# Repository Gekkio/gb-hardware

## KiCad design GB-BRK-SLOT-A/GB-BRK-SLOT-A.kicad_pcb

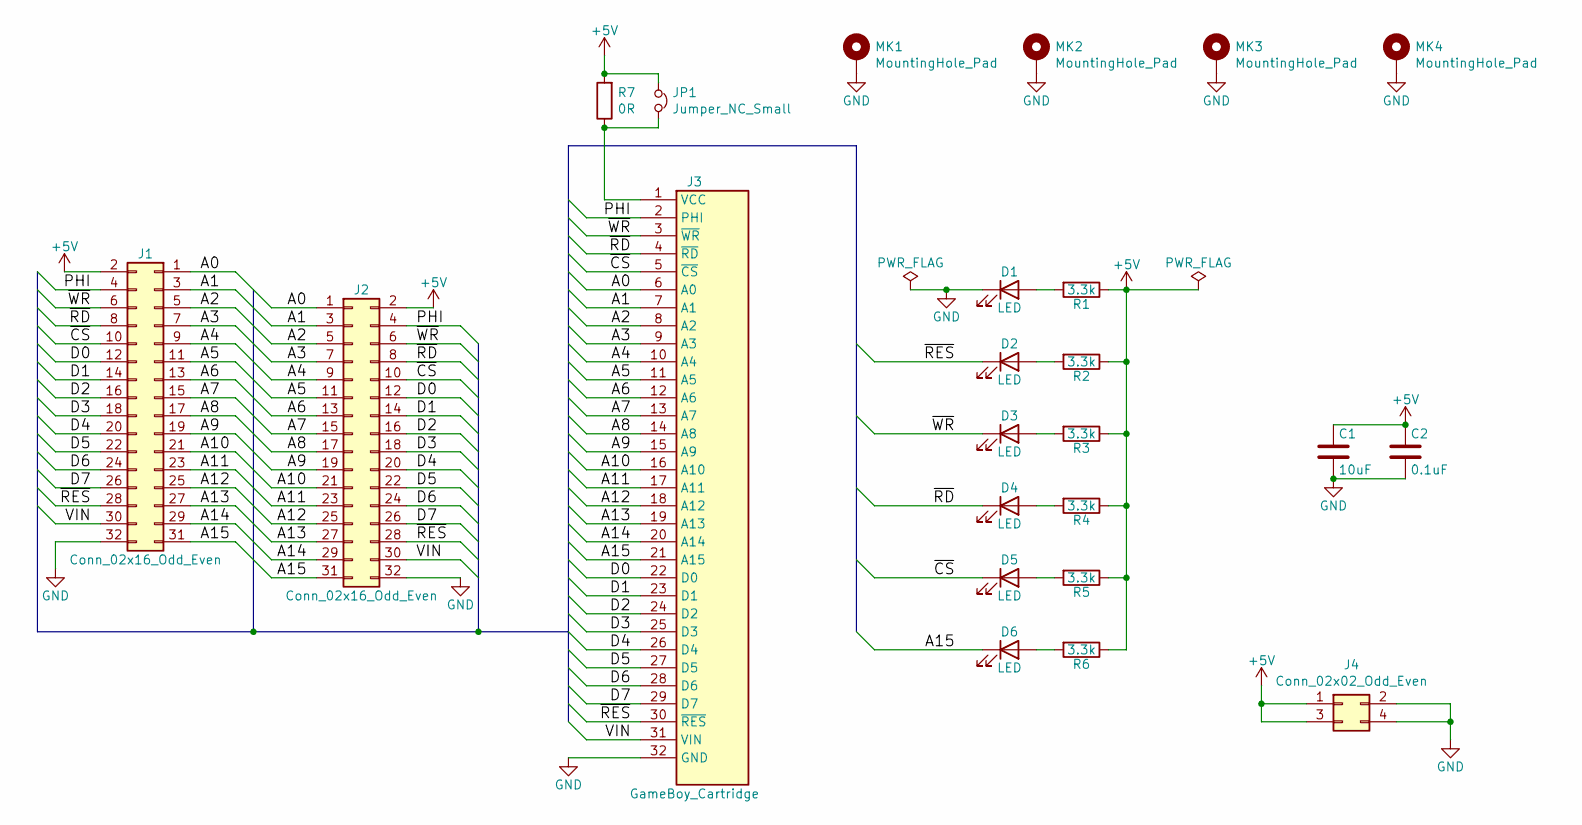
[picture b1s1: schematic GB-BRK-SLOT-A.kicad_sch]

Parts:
C1: 10uF; C_1206_3216Metric
C2: 0.1uF; C_0603_1608Metric
D1, D2, D3, D4, D5, D6: LED; LED_0603_1608Metric
J1: Conn_02x16_Odd_Even; PinSocket_2x16_P2.54mm_Vertical
J2: Conn_02x16_Odd_Even; PinHeader_2x16_P2.54mm_Vertical
J3: GameBoy_Cartridge; GameBoy_Cartridge_DMG_1x32_P1.50mm_Socket_Horizontal
J4: Conn_02x02_Odd_Even; PinHeader_2x02_P2.54mm_Vertical
JP1: Jumper_NC_Small; PinHeader_1x02_P2.54mm_Vertical
MK1, MK2, MK3, MK4: MountingHole_Pad; MountingHole_3.2mm_M3_Pad_Via
R1, R2, R3, R4, R5, R6: 3.3k; R_0603_1608Metric
R7: 0R; R_1206_3216Metric_Pad1.42x1.75mm_HandSolder

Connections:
+5V: C1.1, C2.1, J1.2, J2.2, J4.1, J4.3, JP1.1, R1.1, R2.1, R3.1, R4.1, R5.1, R6.1, R7.2
/A0: J1.1, J2.1, J3.6 (A0)
/A1: J1.3, J2.3, J3.7 (A1)
/A2: J1.5, J2.5, J3.8 (A2)
/A3: J1.7, J2.7, J3.9 (A3)
/A4: J1.9, J2.9, J3.10 (A4)
/A5: J1.11, J2.11, J3.11 (A5)
/A6: J1.13, J2.13, J3.12 (A6)
/A7: J1.15, J2.15, J3.13 (A7)
/A8: J1.17, J2.17, J3.14 (A8)
/A9: J1.19, J2.19, J3.15 (A9)
/A10: J1.21, J2.21, J3.16 (A10)
/A11: J1.23, J2.23, J3.17 (A11)
/A12: J1.25, J2.25, J3.18 (A12)
/A13: J1.27, J2.27, J3.19 (A13)
/A14: J1.29, J2.29, J3.20 (A14)
/A15: D6.1 (K), J1.31, J2.31, J3.21 (A15)
/D0: J1.12, J2.12, J3.22 (D0)
/D1: J1.14, J2.14, J3.23 (D1)
/D2: J1.16, J2.16, J3.24 (D2)
/D3: J1.18, J2.18, J3.25 (D3)
/D4: J1.20, J2.20, J3.26 (D4)
/D5: J1.22, J2.22, J3.27 (D5)
/D6: J1.24, J2.24, J3.28 (D6)
/D7: J1.26, J2.26, J3.29 (D7)
/PHI: J1.4, J2.4, J3.2 (PHI)
/VIN: J1.30, J2.30, J3.31 (VIN)
/~CS: D5.1 (K), J1.10, J2.10, J3.5 (~CS)
/~RD: D4.1 (K), J1.8, J2.8, J3.4 (~RD)
/~RES: D2.1 (K), J1.28, J2.28, J3.30 (~RES)
/~WR: D3.1 (K), J1.6, J2.6, J3.3 (~WR)
GND: C1.2, C2.2, D1.1 (K), J1.32, J2.32, J3.32 (GND), J4.2, J4.4, MK1.1, MK2.1, MK3.1, MK4.1
unnamed: D1.2 (A), R1.2
unnamed: D2.2 (A), R2.2
unnamed: D3.2 (A), R3.2
unnamed: D4.2 (A), R4.2
unnamed: D5.2 (A), R5.2
unnamed: D6.2 (A), R6.2
unnamed: J3.1 (VCC), JP1.2, R7.1

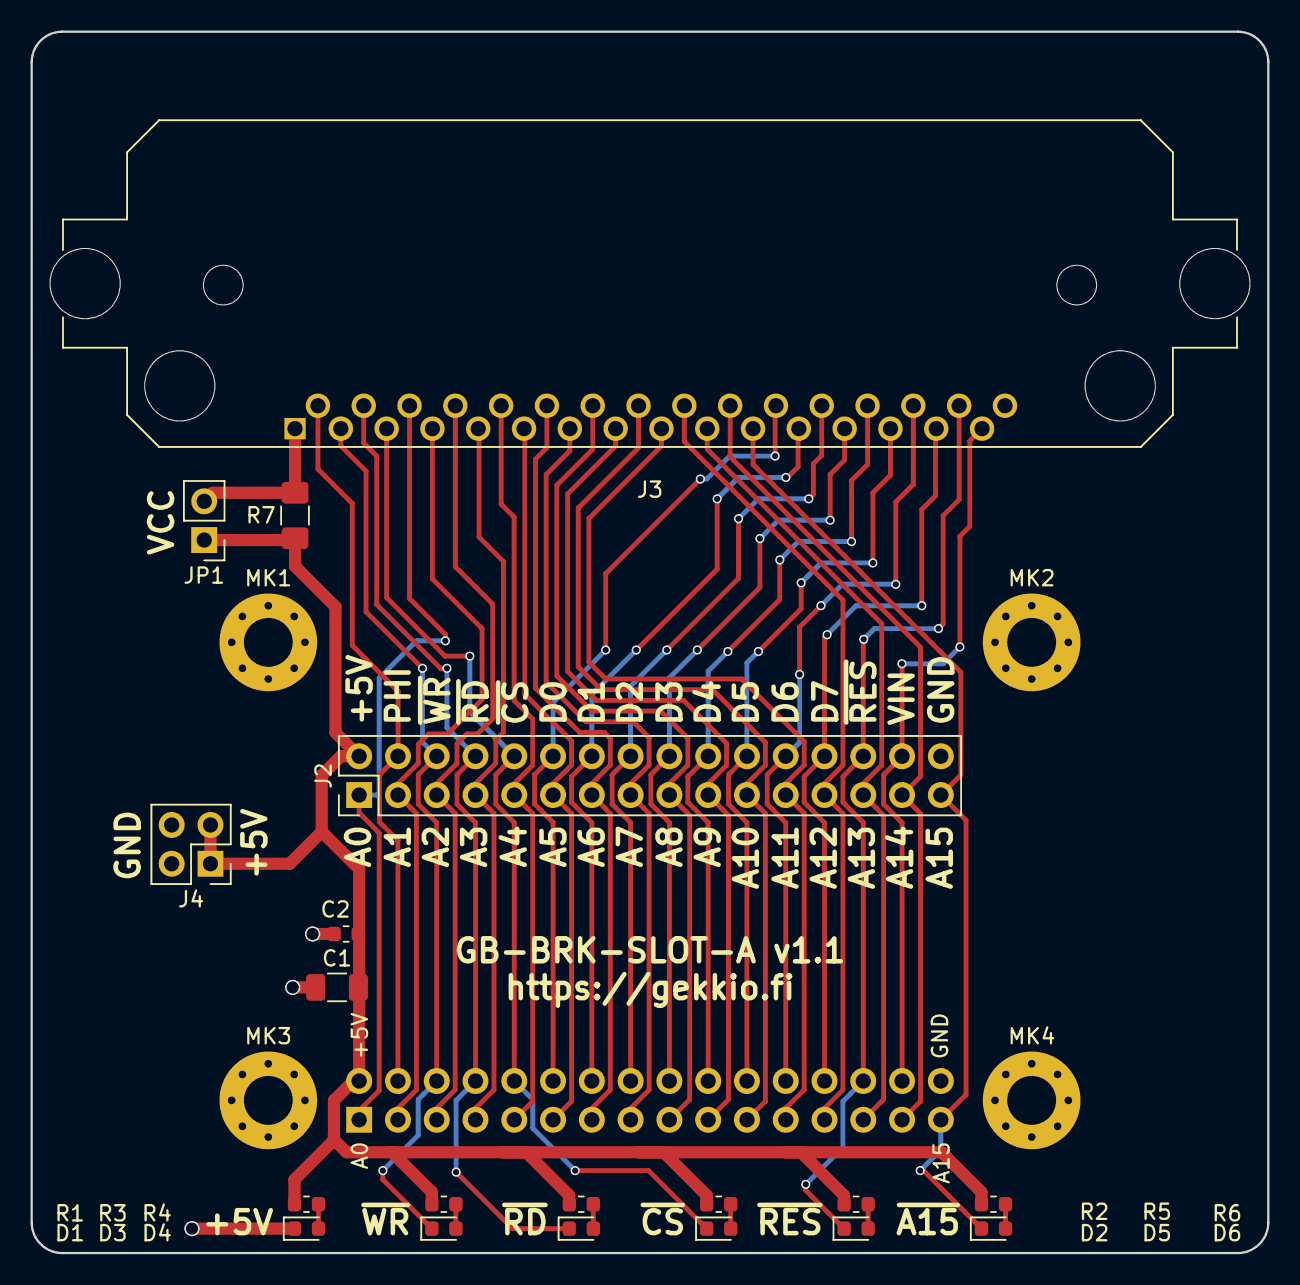
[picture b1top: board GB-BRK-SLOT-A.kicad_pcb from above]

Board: 2 copper layers, 81.0 x 80.0 mm, 24 parts (1 on the bottom side), 39 nets.

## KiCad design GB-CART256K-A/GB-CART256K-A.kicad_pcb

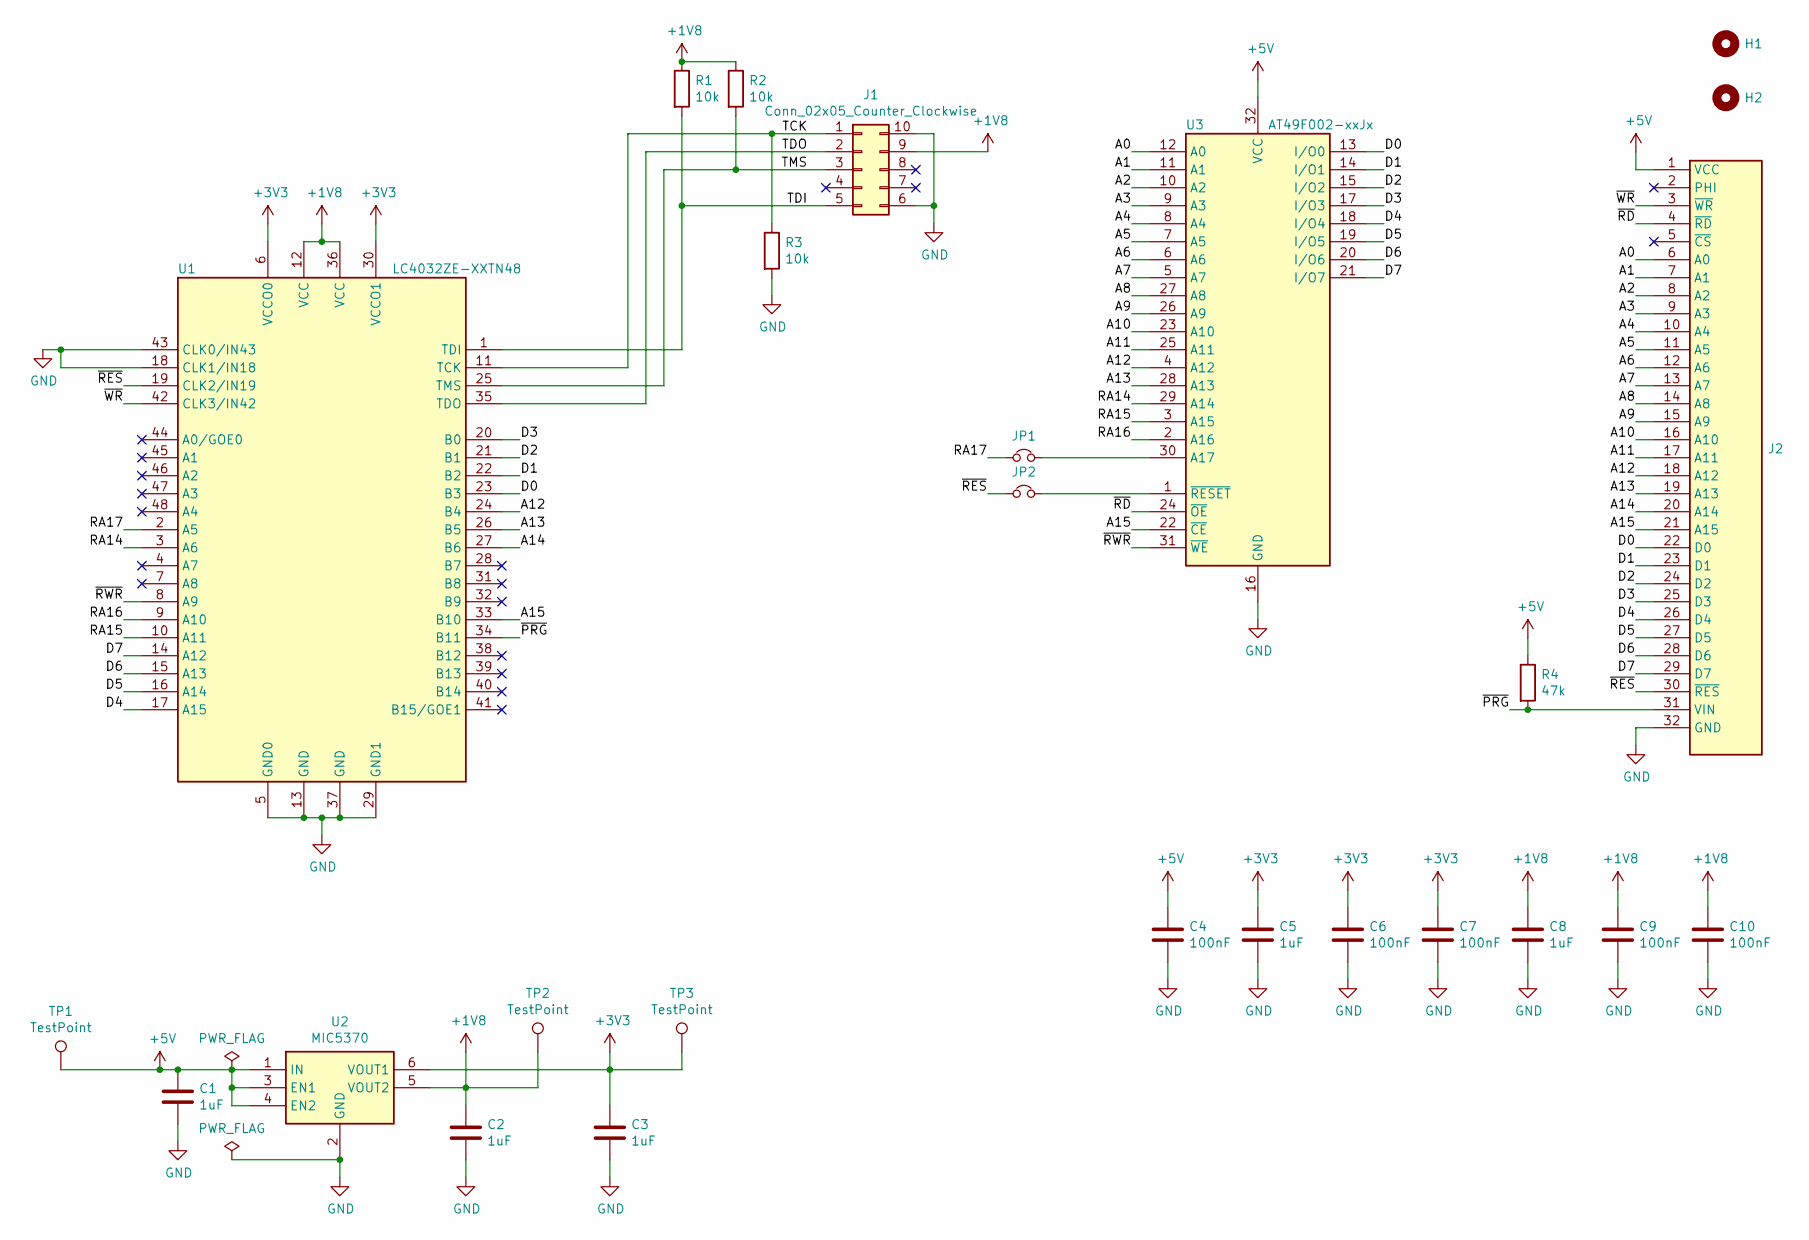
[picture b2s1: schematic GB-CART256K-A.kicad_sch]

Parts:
C1, C2, C3, C5, C8: 1uF; C_0805_2012Metric
C4, C6, C7, C9, C10: 100nF; C_0603_1608Metric
H1: DNF; MountingHole_7.2mm
H2: DNF; MountingHole_2.3mm
J1: Conn_02x05_Counter_Clockwise; Tag-Connect_TC2050-IDC-NL_2x05_P1.27mm_Vertical
J2: DNF; GameBoy_Cartridge_1x32_P1.50mm_Edge
JP1, JP2: DNF; SolderJumper-2_P1.3mm_Open_RoundedPad1.0x1.5mm
R1, R2, R3: 10k; R_0603_1608Metric
R4: 47k; R_0603_1608Metric
TP1, TP2, TP3: TestPoint; TestPoint_THTPad_D2.0mm_Drill1.0mm
U1: LC4032ZE-XXTN48; TQFP-48_7x7mm_P0.5mm
U2: MIC5370; MLF-6-1EP_1.6x1.6mm_P0.5mm_EP0.5x1.26mm
U3: AT49F002-xxJx; PLCC-32_11.4x14.0mm_P1.27mm

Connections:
+1V8: C2.1, C8.1, C9.1, C10.1, J1.9, R1.1, R2.1, TP2.1, U1.12 (VCC), U1.36 (VCC), U2.5 (VOUT2)
+3V3: C3.1, C5.1, C6.1, C7.1, TP3.1, U1.6 (VCCO0), U1.30 (VCCO1), U2.6 (VOUT1)
+5V: C1.1, C4.1, J2.1 (VCC), R4.1, TP1.1, U2.1 (IN), U2.3 (EN1), U2.4 (EN2), U3.32 (VCC)
/A0: J2.6 (A0), U3.12 (A0)
/A1: J2.7 (A1), U3.11 (A1)
/A2: J2.8 (A2), U3.10 (A2)
/A3: J2.9 (A3), U3.9 (A3)
/A4: J2.10 (A4), U3.8 (A4)
/A5: J2.11 (A5), U3.7 (A5)
/A6: J2.12 (A6), U3.6 (A6)
/A7: J2.13 (A7), U3.5 (A7)
/A8: J2.14 (A8), U3.27 (A8)
/A9: J2.15 (A9), U3.26 (A9)
/A10: J2.16 (A10), U3.23 (A10)
/A11: J2.17 (A11), U3.25 (A11)
/A12: J2.18 (A12), U1.24 (B4), U3.4 (A12)
/A13: J2.19 (A13), U1.26 (B5), U3.28 (A13)
/A14: J2.20 (A14), U1.27 (B6)
/A15: J2.21 (A15), U1.33 (B10), U3.22 (~CE)
/D0: J2.22 (D0), U1.23 (B3), U3.13 (I/O0)
/D1: J2.23 (D1), U1.22 (B2), U3.14 (I/O1)
/D2: J2.24 (D2), U1.21 (B1), U3.15 (I/O2)
/D3: J2.25 (D3), U1.20 (B0), U3.17 (I/O3)
/D4: J2.26 (D4), U1.17 (A15), U3.18 (I/O4)
/D5: J2.27 (D5), U1.16 (A14), U3.19 (I/O5)
/D6: J2.28 (D6), U1.15 (A13), U3.20 (I/O6)
/D7: J2.29 (D7), U1.14 (A12), U3.21 (I/O7)
/RA14: U1.3 (A6), U3.29 (A14)
/RA15: U1.10 (A11), U3.3 (A15)
/RA16: U1.9 (A10), U3.2 (A16)
/RA17: JP1.1, U1.2 (A5)
/TCK: J1.1, R3.1, U1.11 (TCK)
/TDI: J1.5, R1.2, U1.1 (TDI)
/TDO: J1.2, U1.35 (TDO)
/TMS: J1.3, R2.2, U1.25 (TMS)
/~PRG: J2.31 (VIN), R4.2, U1.34 (B11)
/~RD: J2.4 (~RD), U3.24 (~OE)
/~RES: J2.30 (~RES), JP2.1, U1.19 (CLK2/IN19)
/~RWR: U1.8 (A9), U3.31 (~WE)
/~WR: J2.3 (~WR), U1.42 (CLK3/IN42)
GND: C1.2, C2.2, C3.2, C4.2, C5.2, C6.2, C7.2, C8.2, C9.2, C10.2, J1.6, J1.10, J2.32 (GND), R3.2, U1.5 (GND0), U1.13 (GND), U1.18 (CLK1/IN18), U1.29 (GND1), U1.37 (GND), U1.43 (CLK0/IN43), U2.2 (GND), U2.7 (GND), U3.16 (GND)
unnamed: JP1.2, U3.30 (A17)
unnamed: JP2.2, U3.1 (~RESET)

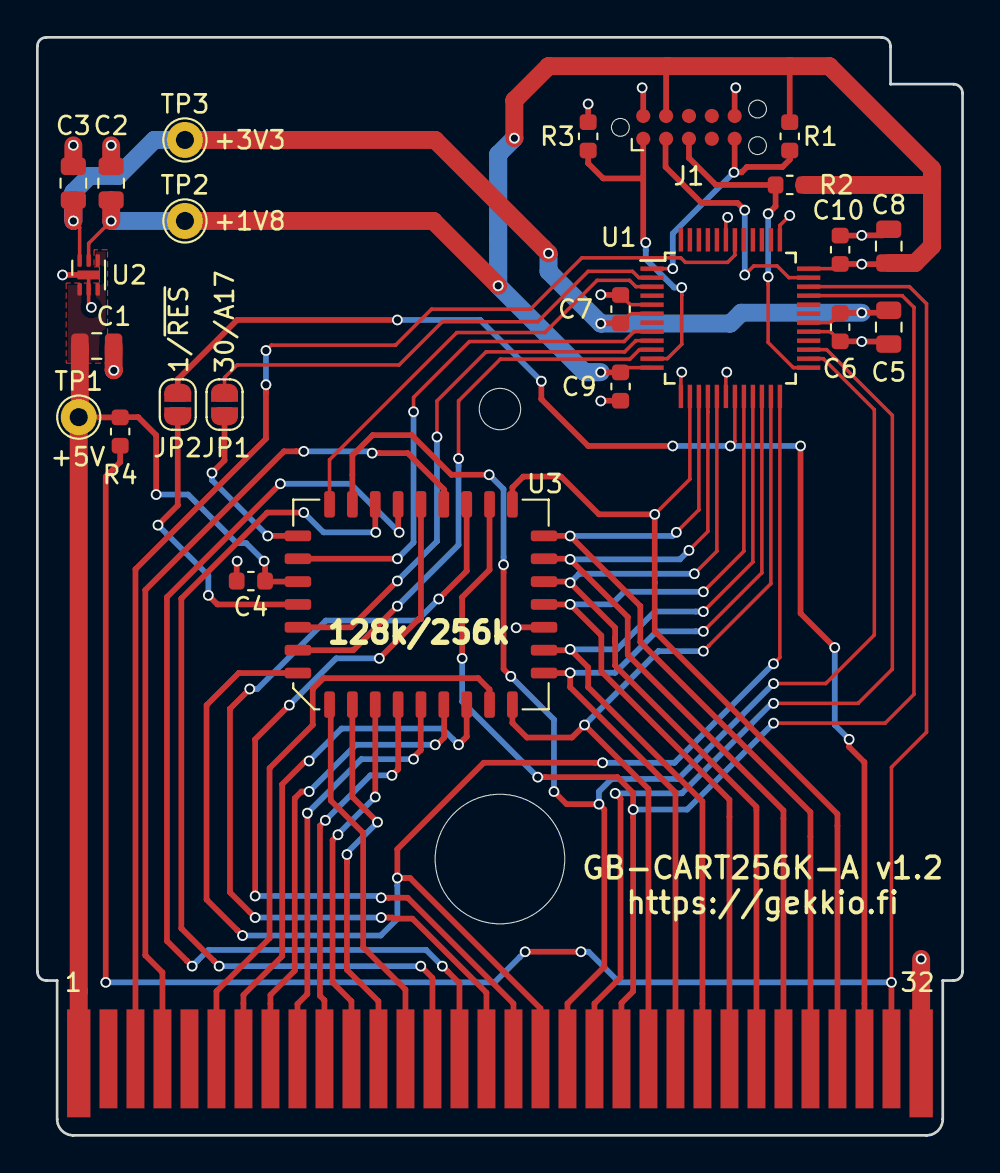
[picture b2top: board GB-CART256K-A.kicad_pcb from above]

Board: 2 copper layers, 51.4 x 61.0 mm, 26 parts (0 on the bottom side), 43 nets.

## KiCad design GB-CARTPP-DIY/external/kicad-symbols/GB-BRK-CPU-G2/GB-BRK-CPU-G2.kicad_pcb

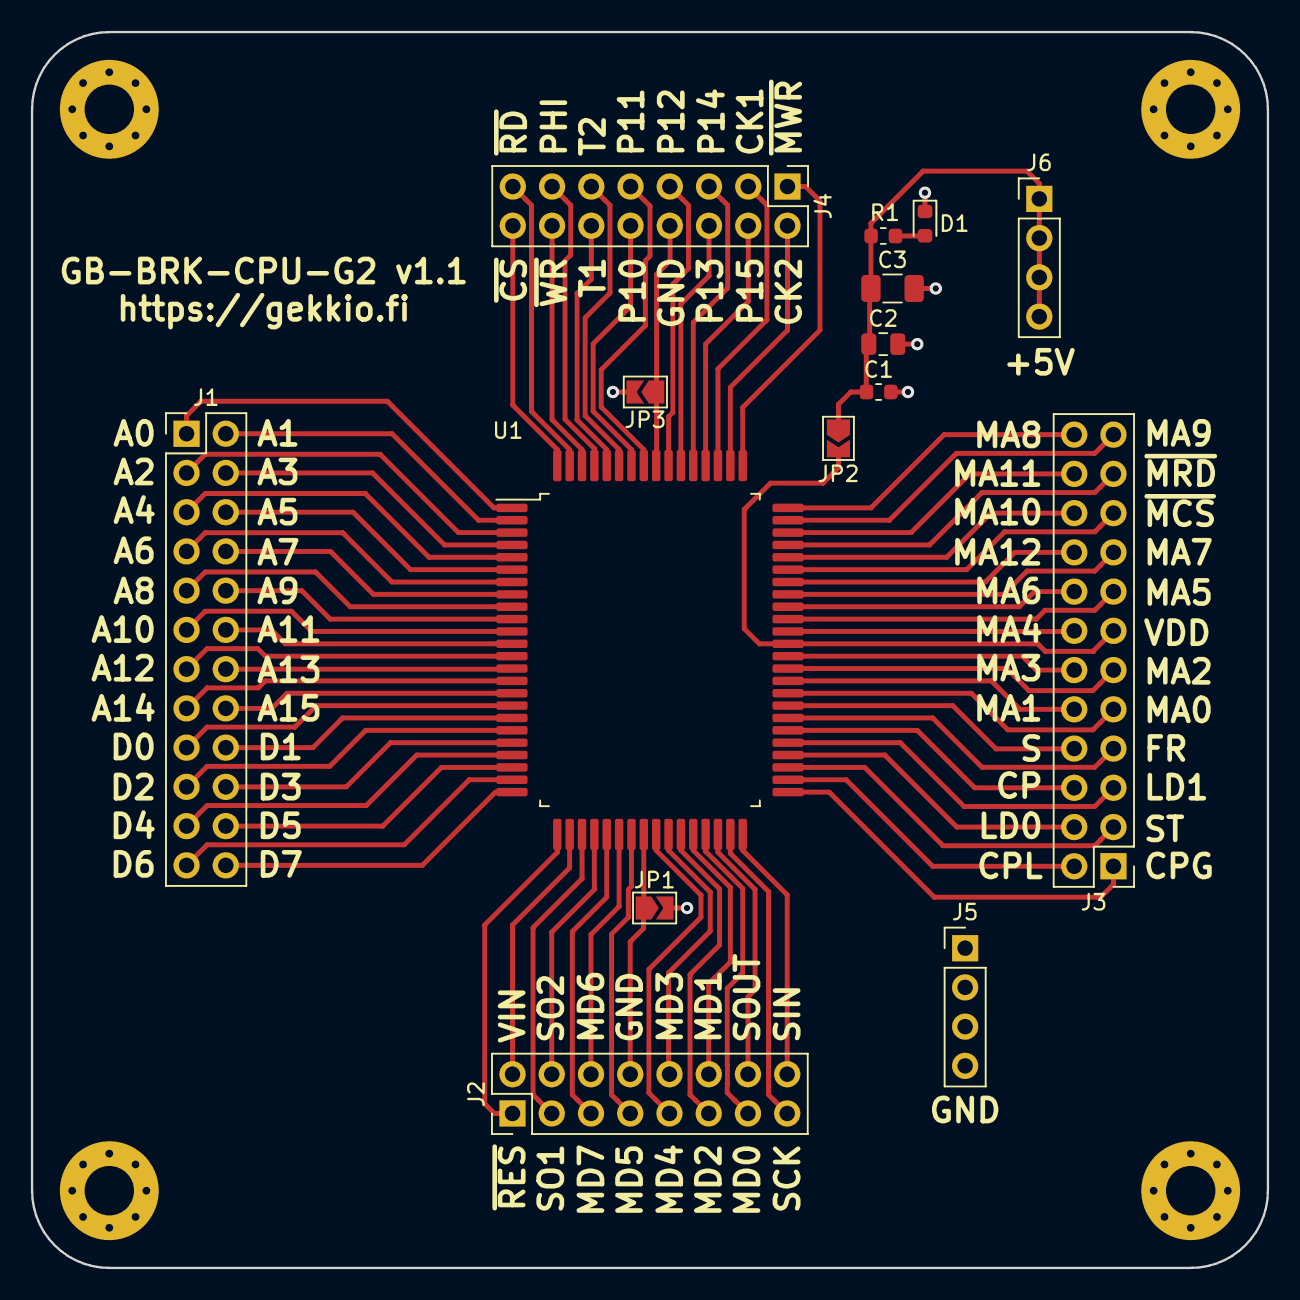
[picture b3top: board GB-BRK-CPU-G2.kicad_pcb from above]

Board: 2 copper layers, 80.0 x 80.0 mm, 19 parts (0 on the bottom side), 83 nets.

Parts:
C1: 0.1uF; C_0603_1608Metric
C2: 1uF; C_0805_2012Metric
C3: 10uF; C_1206_3216Metric
D1: LED; LED_0603_1608Metric
J1, J3: Conn_02x12_Top_Bottom; PinHeader_2x12_P2.54mm_Vertical
J2, J4: Conn_02x08_Top_Bottom; PinHeader_2x08_P2.54mm_Vertical
J5, J6: Conn_01x04; PinHeader_1x04_P2.54mm_Vertical
JP1, JP2, JP3: Jumper; SolderJumper-2_P1.3mm_Open_TrianglePad1.0x1.5mm
MK1, MK2, MK3, MK4: MountingHole_Pad; MountingHole_3.2mm_M3_Pad_Via
R1: 3.3k; R_0603_1608Metric
U1: GameBoy_CPU_DMG-SGB; Sharp_QFP-80_14x20mm_P0.8mm

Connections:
+5V: C1.1, C2.1, C3.1, J6.1, J6.2, J6.3, J6.4, JP2.1, R1.2
/Pin_1: J1.1, U1.1
/Pin_2: J1.2, U1.2
/Pin_3: J1.3, U1.3
/Pin_4: J1.4, U1.4
/Pin_5: J1.5, U1.5
/Pin_6: J1.6, U1.6
/Pin_7: J1.7, U1.7
/Pin_8: J1.8, U1.8
/Pin_9: J1.9, U1.9
/Pin_10: J1.10, U1.10
/Pin_11: J1.11, U1.11
/Pin_12: J1.12, U1.12
/Pin_13: J1.13, U1.13
/Pin_14: J1.14, U1.14
/Pin_15: J1.15, U1.15
/Pin_16: J1.16, U1.16
/Pin_17: J1.17, U1.17
/Pin_18: J1.18, U1.18
/Pin_19: J1.19, U1.19
/Pin_20: J1.20, U1.20
/Pin_21: J1.21, U1.21
/Pin_22: J1.22, U1.22
/Pin_23: J1.23, U1.23
/Pin_24: J1.24, U1.24
/Pin_25: J2.1, U1.25
/Pin_26: J2.2, U1.26
/Pin_27: J2.3, U1.27
/Pin_28: J2.4, U1.28
/Pin_29: J2.5, U1.29
/Pin_30: J2.6, U1.30
/Pin_31: J2.7, U1.31
/Pin_32: J2.8, JP1.1, U1.32
/Pin_33: J2.9, U1.33
/Pin_34: J2.10, U1.34
/Pin_35: J2.11, U1.35
/Pin_36: J2.12, U1.36
/Pin_37: J2.13, U1.37
/Pin_38: J2.14, U1.38
/Pin_39: J2.15, U1.39
/Pin_40: J2.16, U1.40
/Pin_41: J3.1, U1.41
/Pin_42: J3.2, U1.42
/Pin_43: J3.3, U1.43
/Pin_44: J3.4, U1.44
/Pin_45: J3.5, U1.45
/Pin_46: J3.6, U1.46
/Pin_47: J3.7, U1.47
/Pin_48: J3.8, U1.48
/Pin_49: J3.9, U1.49
/Pin_50: J3.10, U1.50
/Pin_51: J3.11, U1.51
/Pin_52: J3.12, U1.52
/Pin_53: J3.13, JP2.2, U1.53
/Pin_54: J3.14, U1.54
/Pin_55: J3.15, U1.55
/Pin_56: J3.16, U1.56
/Pin_57: J3.17, U1.57
/Pin_58: J3.18, U1.58
/Pin_59: J3.19, U1.59
/Pin_60: J3.20, U1.60
/Pin_61: J3.21, U1.61
/Pin_62: J3.22, U1.62
/Pin_63: J3.23, U1.63
/Pin_64: J3.24, U1.64
/Pin_65: J4.1, U1.65
/Pin_66: J4.2, U1.66
/Pin_67: J4.3, U1.67
/Pin_68: J4.4, U1.68
/Pin_69: J4.5, U1.69
/Pin_70: J4.6, U1.70
/Pin_71: J4.7, U1.71
/Pin_72: J4.8, JP3.1, U1.72
/Pin_73: J4.9, U1.73
/Pin_74: J4.10, U1.74
/Pin_75: J4.11, U1.75
/Pin_76: J4.12, U1.76
/Pin_77: J4.13, U1.77
/Pin_78: J4.14, U1.78
/Pin_79: J4.15, U1.79
/Pin_80: J4.16, U1.80
GND: C1.2, C2.2, C3.2, D1.1, J5.1, J5.2, J5.3, J5.4, JP1.2, JP3.2, MK1.1, MK2.1, MK3.1, MK4.1
unnamed: D1.2, R1.1

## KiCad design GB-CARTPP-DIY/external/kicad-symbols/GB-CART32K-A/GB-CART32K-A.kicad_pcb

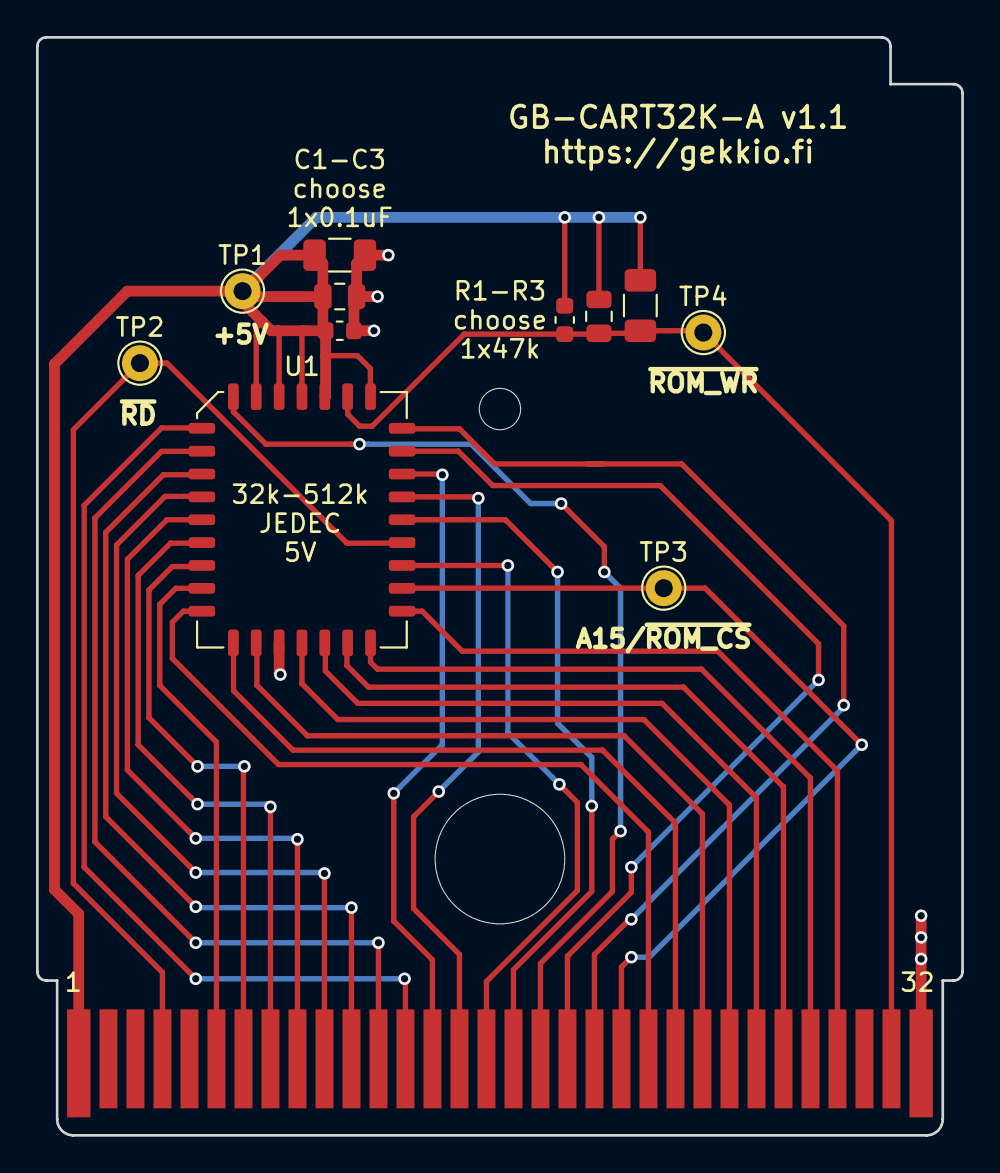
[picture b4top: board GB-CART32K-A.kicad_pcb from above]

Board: 2 copper layers, 51.4 x 61.0 mm, 14 parts (0 on the bottom side), 28 nets.

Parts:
C1: 0.1uF; C_0603_1608Metric
C2: 1uF; C_0805_2012Metric
C3: 10uF; C_1206_3216Metric
H1: DNF; MountingHole_7.2mm
H2: DNF; MountingHole_2.3mm
J1: DNF; GameBoy_Cartridge_1x32_P1.50mm_Edge
R1: 47k; R_0603_1608Metric
R2: 47k; R_0805_2012Metric
R3: 47k; R_1206_3216Metric
TP1, TP2, TP3, TP4: TestPoint; TestPoint_THTPad_D2.0mm_Drill1.0mm
U1: SST39SF040; PLCC-32_11.4x14.0mm_P1.27mm

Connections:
+5V: C1.1, C2.1, C3.1, J1.1, R1.1, R2.1, R3.1, TP1.1, U1.1, U1.2, U1.3, U1.30, U1.32
/A0: J1.6, U1.12
/A1: J1.7, U1.11
/A2: J1.8, U1.10
/A3: J1.9, U1.9
/A4: J1.10, U1.8
/A5: J1.11, U1.7
/A6: J1.12, U1.6
/A7: J1.13, U1.5
/A8: J1.14, U1.27
/A9: J1.15, U1.26
/A10: J1.16, U1.23
/A11: J1.17, U1.25
/A12: J1.18, U1.4
/A13: J1.19, U1.28
/A14: J1.20, U1.29
/D0: J1.22, U1.13
/D1: J1.23, U1.14
/D2: J1.24, U1.15
/D3: J1.25, U1.17
/D4: J1.26, U1.18
/D5: J1.27, U1.19
/D6: J1.28, U1.20
/D7: J1.29, U1.21
/~RD: J1.4, TP2.1, U1.24
/~ROM_CS: J1.21, TP3.1, U1.22
/~ROM_WR: J1.31, R1.2, R2.2, R3.2, TP4.1, U1.31
GND: C1.2, C2.2, C3.2, J1.32, U1.16

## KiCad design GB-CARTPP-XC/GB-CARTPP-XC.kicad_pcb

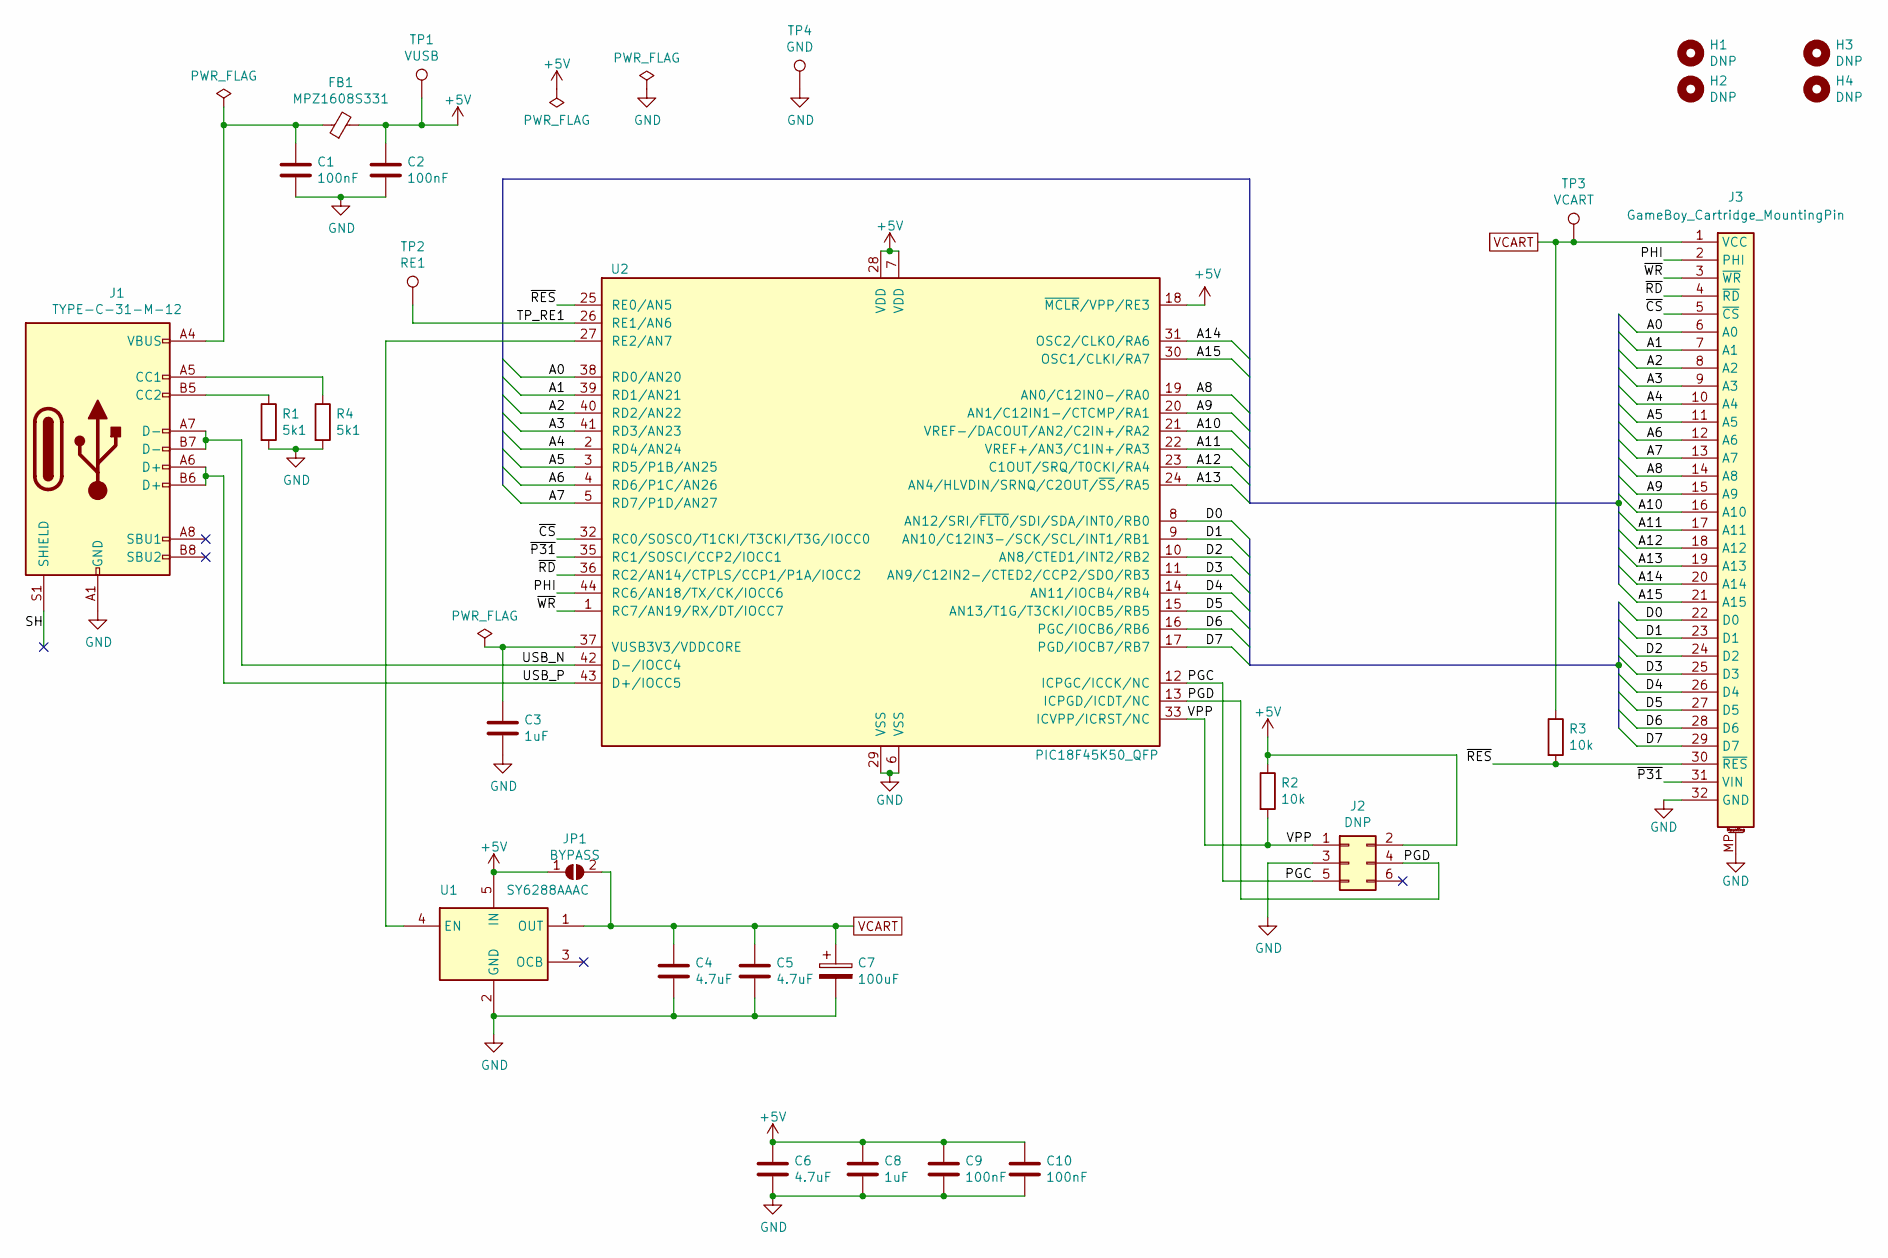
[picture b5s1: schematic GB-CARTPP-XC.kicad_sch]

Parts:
C1, C2, C9, C10: 100nF; C_0603_1608Metric
C3, C8: 1uF; C_0805_2012Metric
C4, C5, C6: 4.7uF; C_0805_2012Metric
C7: 100uF; CP_Elec_6.3x5.8
FB1: MPZ1608S331; L_0603_1608Metric
H1, H2, H3, H4: DNP; MountingHole_3.2mm_M3
J1: TYPE-C-31-M-12; USB_C_Receptacle_HRO_TYPE-C-31-M-12
J2: DNP; Tag-Connect_TC2030-IDC-NL_2x03_P1.27mm_Vertical
J3: GameBoy_Cartridge_MountingPin; GameBoy_Cartridge_AGS_1x32-1MP_P1.50mm_Socket_Horizontal
JP1: BYPASS; SolderJumper-2_P1.3mm_Open_RoundedPad1.0x1.5mm
R1, R4: 5k1; R_0603_1608Metric
R2, R3: 10k; R_0603_1608Metric
TP1: VUSB; TestPoint_THTPad_D2.0mm_Drill1.0mm
TP2: RE1; TestPoint_Pad_D1.0mm
TP3: VCART; TestPoint_THTPad_D2.0mm_Drill1.0mm
TP4: GND; TestPoint_THTPad_D2.0mm_Drill1.0mm
U1: SY6288AAAC; SOT-23-5
U2: PIC18F45K50_QFP; TQFP-44_10x10mm_P0.8mm

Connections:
+5V: C2.1, C6.1, C8.1, C9.1, C10.1, FB1.2, J2.2, JP1.1 (A), R2.1, TP1.1, U1.5 (IN), U2.7 (VDD), U2.18 (~MCLR/VPP/RE3), U2.28 (VDD)
/A0: J3.6 (A0), U2.38 (RD0/AN20)
/A1: J3.7 (A1), U2.39 (RD1/AN21)
/A2: J3.8 (A2), U2.40 (RD2/AN22)
/A3: J3.9 (A3), U2.41 (RD3/AN23)
/A4: J3.10 (A4), U2.2 (RD4/AN24)
/A5: J3.11 (A5), U2.3 (RD5/P1B/AN25)
/A6: J3.12 (A6), U2.4 (RD6/P1C/AN26)
/A7: J3.13 (A7), U2.5 (RD7/P1D/AN27)
/A8: J3.14 (A8), U2.19 (AN0/C12IN0-/RA0)
/A9: J3.15 (A9), U2.20 (AN1/C12IN1-/CTCMP/RA1)
/A10: J3.16 (A10), U2.21 (VREF-/DACOUT/AN2/C2IN+/RA2)
/A11: J3.17 (A11), U2.22 (VREF+/AN3/C1IN+/RA3)
/A12: J3.18 (A12), U2.23 (C1OUT/SRQ/T0CKI/RA4)
/A13: J3.19 (A13), U2.24 (AN4/HLVDIN/SRNQ/C2OUT/~SS/RA5)
/A14: J3.20 (A14), U2.31 (OSC2/CLKO/RA6)
/A15: J3.21 (A15), U2.30 (OSC1/CLKI/RA7)
/D0: J3.22 (D0), U2.8 (AN12/SRI/~FLT0/SDI/SDA/INT0/RB0)
/D1: J3.23 (D1), U2.9 (AN10/C12IN3-/SCK/SCL/INT1/RB1)
/D2: J3.24 (D2), U2.10 (AN8/CTED1/INT2/RB2)
/D3: J3.25 (D3), U2.11 (AN9/C12IN2-/CTED2/CCP2/SDO/RB3)
/D4: J3.26 (D4), U2.14 (AN11/IOCB4/RB4)
/D5: J3.27 (D5), U2.15 (AN13/T1G/T3CKI/IOCB5/RB5)
/D6: J3.28 (D6), U2.16 (PGC/IOCB6/RB6)
/D7: J3.29 (D7), U2.17 (PGD/IOCB7/RB7)
/PGC: J2.5, U2.12 (ICPGC/ICCK/NC)
/PGD: J2.4, U2.13 (ICPGD/ICDT/NC)
/PHI: J3.2 (PHI), U2.44 (RC6/AN18/TX/CK/IOCC6)
/SH: J1.S1 (SHIELD)
/TP_RE1: TP2.1, U2.26 (RE1/AN6)
/USB_N: J1.A7 (D-), J1.B7 (D-), U2.42 (D-/IOCC4)
/USB_P: J1.A6 (D+), J1.B6 (D+), U2.43 (D+/IOCC5)
/VPP: J2.1, R2.2, U2.33 (ICVPP/ICRST/NC)
/~CS: J3.5 (~CS), U2.32 (RC0/SOSCO/T1CKI/T3CKI/T3G/IOCC0)
/~P31: J3.31 (VIN), U2.35 (RC1/SOSCI/CCP2/IOCC1)
/~RD: J3.4 (~RD), U2.36 (RC2/AN14/CTPLS/CCP1/P1A/IOCC2)
/~RES: J3.30 (~RES), R3.2, U2.25 (RE0/AN5)
/~WR: J3.3 (~WR), U2.1 (RC7/AN19/RX/DT/IOCC7)
GND: C1.2, C2.2, C3.2, C4.2, C5.2, C6.2, C7.2, C8.2, C9.2, C10.2, J1.A1 (GND), J1.A12 (GND), J1.B1 (GND), J1.B12 (GND), J2.3, J3.32 (GND), J3.MP, R1.2, R4.2, TP4.1, U1.2 (GND), U2.6 (VSS), U2.29 (VSS)
unnamed: C1.1, FB1.1, J1.A4 (VBUS), J1.A9 (VBUS), J1.B4 (VBUS), J1.B9 (VBUS)
unnamed: C3.1, U2.37 (VUSB3V3/VDDCORE)
unnamed: J1.A5 (CC1), R4.1
unnamed: J1.B5 (CC2), R1.1
unnamed: U1.4 (EN), U2.27 (RE2/AN7)
VCART: C4.1, C5.1, C7.1, J3.1 (VCC), JP1.2 (B), R3.1, TP3.1, U1.1 (OUT)

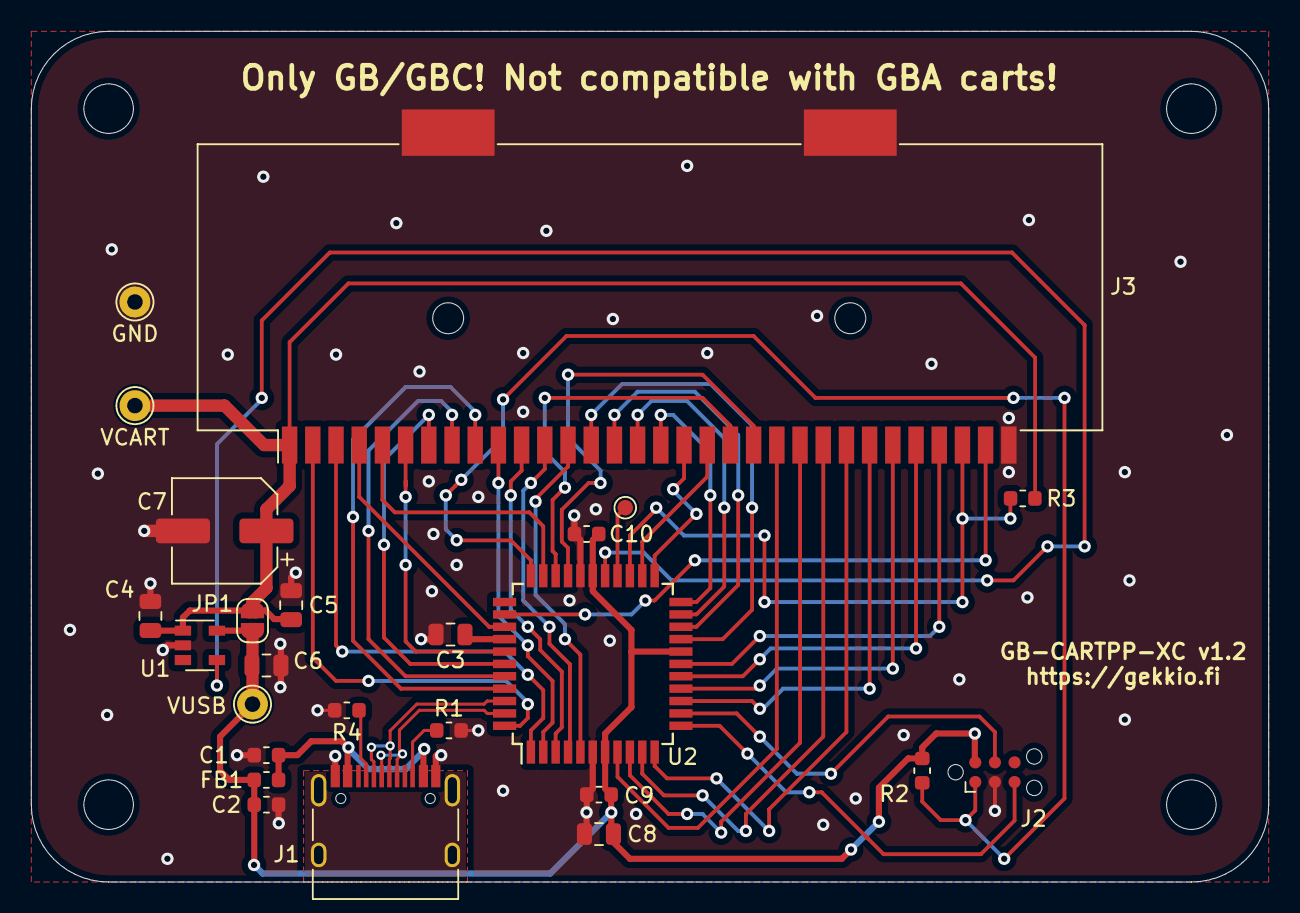
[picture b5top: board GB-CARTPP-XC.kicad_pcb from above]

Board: 2 copper layers, 80.0 x 55.0 mm, 29 parts (0 on the bottom side), 44 nets.
